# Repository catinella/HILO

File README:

#-------------------------------------------------------------------------------------------------------------------------------
#                                                     _   _ ___ _     ___  
#                                                    | | | |_ _| |   / _ \ 
#                                                    | |_| || || |  | | | |
#                                                    |  _  || || |__| |_| |
#                                                    |_| |_|___|_____\___/ 
#                                                     Hardware in the loop
#-------------------------------------------------------------------------------------------------------------------------------

1.0 Files
	firmware    The firmware for manager MCU
	PCB         All the PCBs used in the project
	pcSoftware  The software used to manage the HILO

2.0 Decription
	The goal of this progect is to get a device that allows you to test an electronic system in easy way, by remote too.
	In the 1990 when I was studing at high-scool, who was designed new devices, used generic box with buttons, switches,
	leds, displays.... and so on, to emulate the external environment. Today, unfortunately, many Italian companies still use
	the same deplorable methodology! Due to this approach firmware developers cannot work from their home.

	But the smarter companies use advanced and complicated devices that allow them to test their electronic products remotely,
	in deeper and easier way. These tools are very sophisticated and programmable simulator, where they can simulate the
	external environment is realistic and releiable way. These tools class is calle HILO.

	This project want to provide an economic and very very simple HILO.

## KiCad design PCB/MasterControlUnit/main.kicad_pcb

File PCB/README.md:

## 1.0 Files

|       Files/Dirs      |                         Description                         |
|-----------------------|-------------------------------------------------------------|
| kicadCustomComponents | The KiCAD libraries for the customized symbols/footprints   |
| IOlinesManagement     | The digital I/O lines interface                             |
| ElectricProtections   | I/O Interface electric protection devices                   |
| MasterControlUnit     | The HILO's brain                                            |

## 2.0 Decription
By the hardware points of view, this HILO is composed by the following separated modules. Everyone of them is connected to
the master one using pin-headers connectors and flat-cables.

- The Master Conroller unit interface the I/O lines with the PC and perform the configured tests
- Digital I/O lines interface
- Output lines electrical protection
- (optional) Dedicated to the Analog lines PCB

### 2.1 Components documentation:
- [APS6404L-3SQR-SN](https://eu.mouser.com/datasheet/3/4815/1/APM_PSRAM_E3_QSPI%20(APS6404L-SQH%20KGD_PKG)%20v4.1.pdf)
- [ESP32 WROOM-32-UE](https://www.espressif.com/sites/default/files/documentation/esp32-wroom-32e_esp32-wroom-32ue_datasheet_en.pdf)
- [ESP32-DevKitC-V4](https://docs.espressif.com/projects/esp-idf/en/release-v4.2/esp32/hw-reference/esp32/get-started-devkitc.html)
  [(pinout)](https://docs.espressif.com/projects/esp-idf/en/v5.1/esp32/_images/esp32-devkitC-v4-pinout.png)
- [STM32F407VG](https://www.st.com/resource/en/datasheet/dm00037051.pdf)
- [STM32F407G-DISC1](https://www.st.com/resource/en/data_brief/stm32f4discovery.pdf)
- [MCP23017](https://ww1.microchip.com/downloads/en/DeviceDoc/20001952C.pdf)
- [LD1117S33TR](https://www.st.com/resource/en/datasheet/ld1117.pdf)
- [74HC138](https://www.mouser.com/datasheet/2/308/74hc138.rev1-289073.pdf?srsltid=AU7gw4Xh3rp2TDjylkHruy-TmyljhEpg-pm_lEueWOH79XHFP8UTOZmN)
- [ADA4096-2ARMZ](https://www.analog.com/en/products/ada4096-2.html)

### 2.2 Logic scheme:

## 3.0 GIT sub-modules initialization:
Some great company (e.g., Espressif) provides official KiCad symbols and footprints for their products through public GIT repositories.
To simplify project setup and avoid having to locate and download these repositories manually, I have included them as GIT submodules.
To initialize and download the required submodules, run the following command from the repository root:

	git submodule update --init --recursive

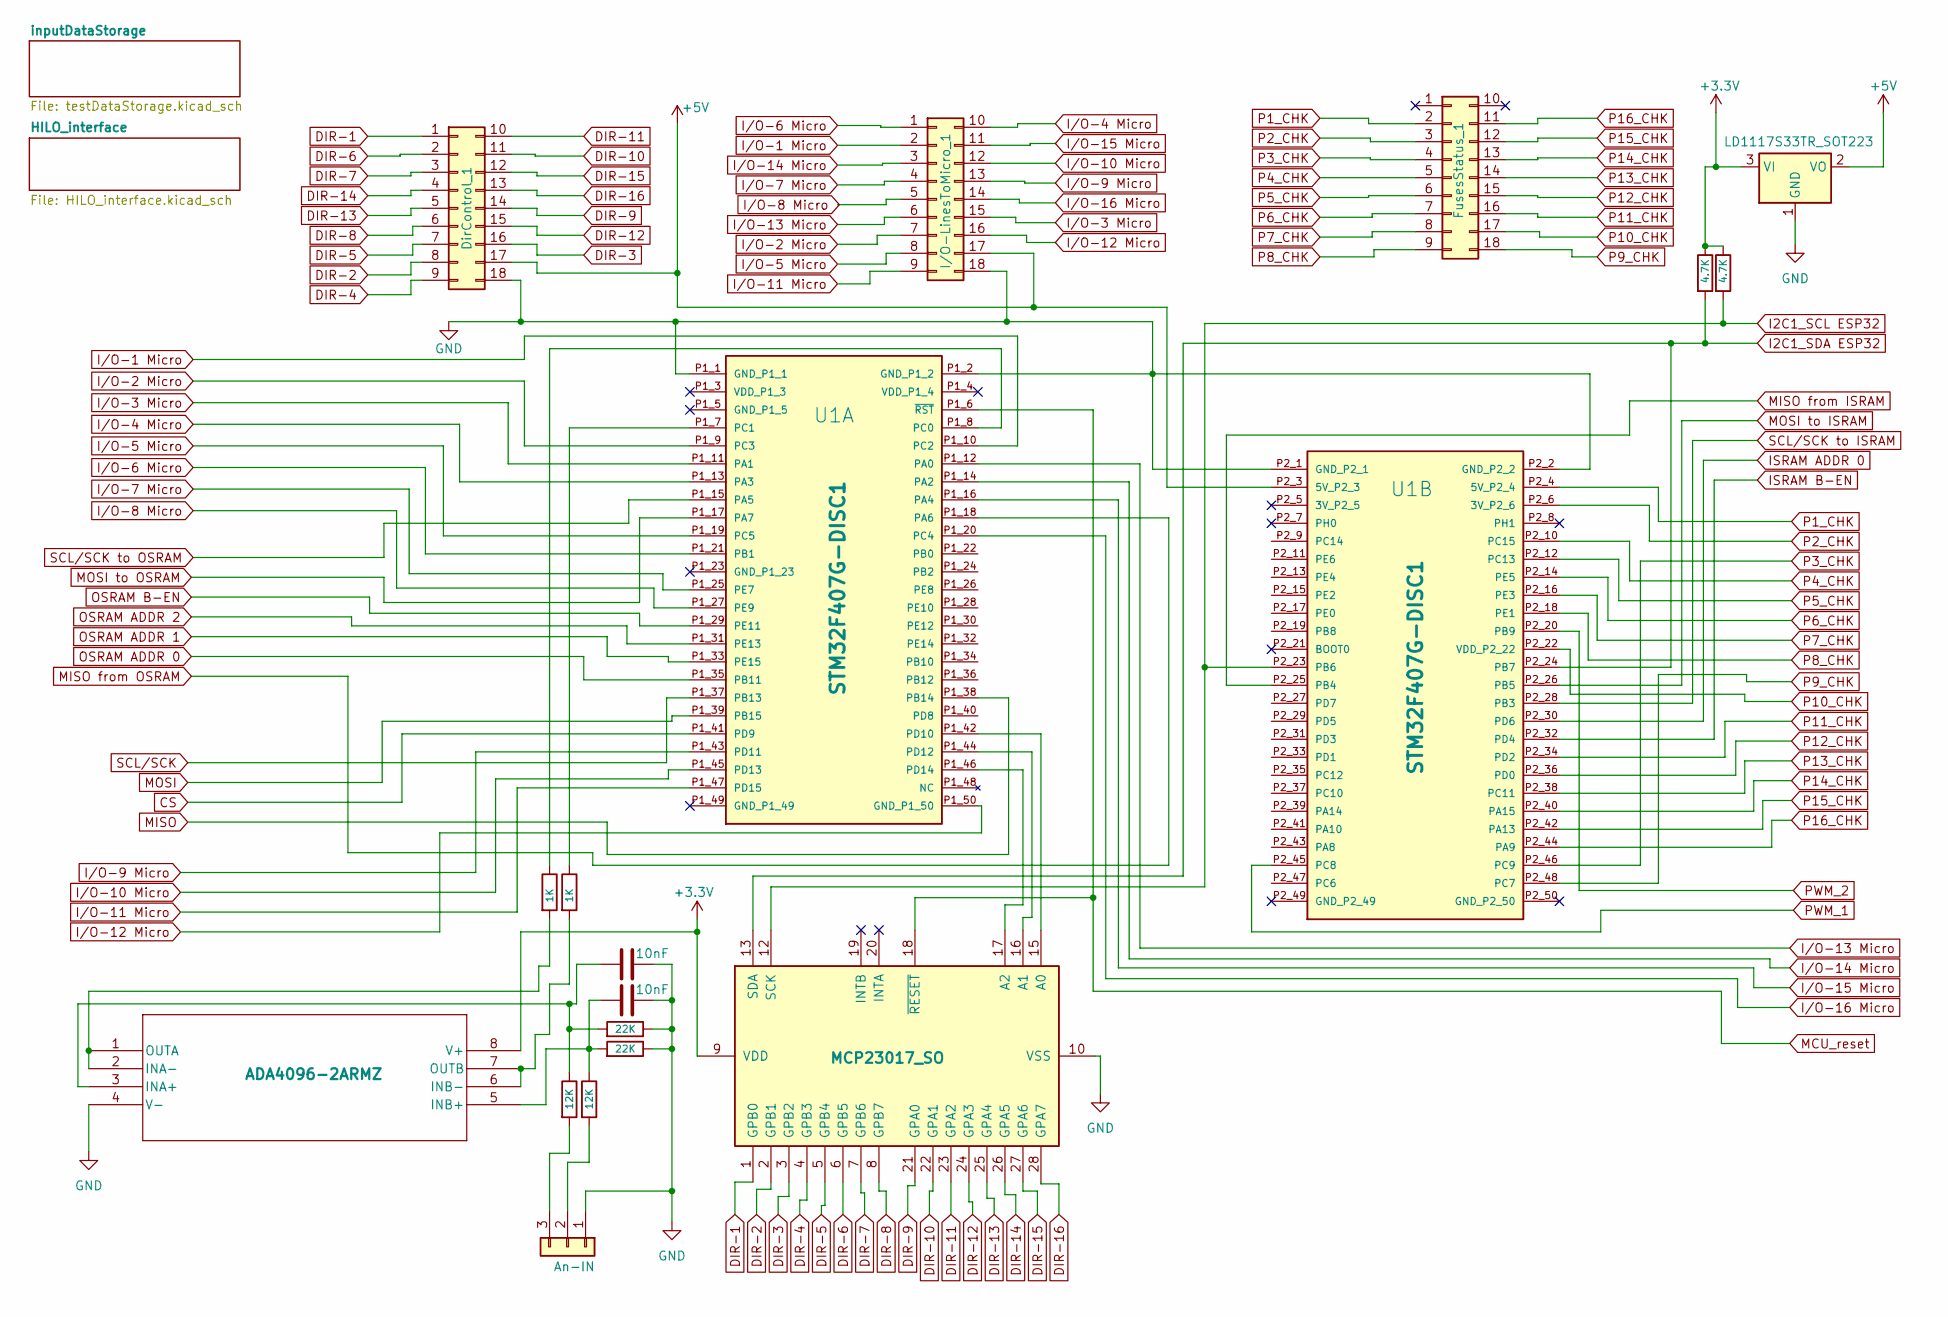
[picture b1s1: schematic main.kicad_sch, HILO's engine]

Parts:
C1, C2: 10nF; CP_Radial_D6.3mm_P2.50mm
DirControl_1: Conn_02x09_Top_Bottom; PinHeader_2x09_P2.54mm_Vertical
FusesStatus_1: Conn_02x09_Top_Bottom; PinHeader_2x09_P2.54mm_Vertical
I/O-LinesToMicro_1: Conn_02x09_Top_Bottom; PinHeader_2x09_P2.54mm_Vertical
J3: An-IN; PinHeader_1x03_P2.54mm_Vertical
R2, R3: 4.7K; R_1206_3216Metric
R4, R5: 12K; R_1206_3216Metric
R6, R7: 1K; R_1206_3216Metric
R8, R9: 22K; R_1206_3216Metric
U1: STM32F407G-DISC1; MODULE_STM32F407G-DISC1; PARTREV 7
U5: LD1117S33TR_SOT223; SOT-223-3_TabPin2
U15: MCP23017_SO; SOIC-28W_7.5x17.9mm_P1.27mm
U17: ADA4096-2ARMZ; RM_8_ADI

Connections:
CS: U1.P1_41 (PD9)
DIR-1: DirControl_1.1, U15.1 (GPB0)
DIR-2: DirControl_1.8, U15.2 (GPB1)
DIR-3: DirControl_1.16, U15.3 (GPB2)
DIR-4: DirControl_1.9, U15.4 (GPB3)
DIR-5: DirControl_1.7, U15.5 (GPB4)
DIR-6: DirControl_1.2, U15.6 (GPB5)
DIR-7: DirControl_1.3, U15.7 (GPB6)
DIR-8: DirControl_1.6, U15.8 (GPB7)
DIR-9: DirControl_1.14, U15.21 (GPA0)
DIR-10: DirControl_1.11, U15.22 (GPA1)
DIR-11: DirControl_1.10, U15.23 (GPA2)
DIR-12: DirControl_1.15, U15.24 (GPA3)
DIR-13: DirControl_1.5, U15.25 (GPA4)
DIR-14: DirControl_1.4, U15.26 (GPA5)
DIR-15: DirControl_1.12, U15.27 (GPA6)
DIR-16: DirControl_1.13, U15.28 (GPA7)
GND: C1.1, C2.1, DirControl_1.18, I/O-LinesToMicro_1.18, J3.1, R8.1, R9.1, U1.P1_1 (GND_P1_1), U1.P1_2 (GND_P1_2), U1.P2_1 (GND_P2_1), U1.P2_2 (GND_P2_2), U5.1 (GND), U15.10 (VSS), U17.4 (V-); also elsewhere on the board
I2C1_SCL ESP32: R3.2, U1.P2_23 (PB6), U15.12 (SCK); also elsewhere on the board
I2C1_SDA ESP32: R2.2, U1.P2_24 (PB7), U15.13 (SDA); also elsewhere on the board
ISRAM ADDR 0: U1.P2_30 (PD6); also elsewhere on the board
ISRAM B-EN: U1.P2_32 (PD4); also elsewhere on the board
I/O-1 Micro: I/O-LinesToMicro_1.2, U1.P1_10 (PC2)
I/O-2 Micro: I/O-LinesToMicro_1.7, U1.P1_9 (PC3)
I/O-3 Micro: I/O-LinesToMicro_1.15, U1.P1_11 (PA1)
I/O-4 Micro: I/O-LinesToMicro_1.10, U1.P1_13 (PA3)
I/O-5 Micro: I/O-LinesToMicro_1.8, U1.P1_19 (PC5)
I/O-6 Micro: I/O-LinesToMicro_1.1, U1.P1_21 (PB1)
I/O-7 Micro: I/O-LinesToMicro_1.4, U1.P1_25 (PE7)
I/O-8 Micro: I/O-LinesToMicro_1.5, U1.P1_27 (PE9)
I/O-9 Micro: I/O-LinesToMicro_1.13, U1.P1_43 (PD11)
I/O-10 Micro: I/O-LinesToMicro_1.12, U1.P1_45 (PD13)
I/O-11 Micro: I/O-LinesToMicro_1.9, U1.P1_47 (PD15)
I/O-12 Micro: I/O-LinesToMicro_1.16, U1.P1_50 (GND_P1_50)
I/O-13 Micro: I/O-LinesToMicro_1.6, U1.P1_12 (PA0)
I/O-14 Micro: I/O-LinesToMicro_1.3, U1.P1_14 (PA2)
I/O-15 Micro: I/O-LinesToMicro_1.11, U1.P1_16 (PA4)
I/O-16 Micro: I/O-LinesToMicro_1.14, U1.P1_20 (PC4)
MCU_reset: U1.P1_6 (~RST), U15.18 (~RESET); also elsewhere on the board
MISO: U1.P1_38 (PB14)
MISO from ISRAM: U1.P2_25 (PB4); also elsewhere on the board
MISO from OSRAM: U1.P1_18 (PA6); also elsewhere on the board
MOSI: U1.P1_39 (PB15)
MOSI to ISRAM: U1.P2_26 (PB5); also elsewhere on the board
MOSI to OSRAM: U1.P1_17 (PA7); also elsewhere on the board
unnamed: J3.2, R5.2
unnamed: J3.3, R4.2
unnamed: R6.1, U1.P1_8 (PC0)
unnamed: R7.1, U1.P1_7 (PC1)
unnamed: U1.P1_42 (PD10), U15.15 (A0)
unnamed: U1.P1_44 (PD12), U15.16 (A1)
unnamed: U1.P1_46 (PD14), U15.17 (A2)
unnamed: C2.2, R4.1, R9.2, U17.3 (INA+)
unnamed: R6.2, U17.1 (OUTA), U17.2 (INA-)
unnamed: C1.2, R5.1, R8.2, U17.5 (INB+)
unnamed: R7.2, U17.6 (INB-), U17.7 (OUTB)
OSRAM ADDR 0: U1.P1_35 (PB11); also elsewhere on the board
OSRAM ADDR 1: U1.P1_33 (PE15); also elsewhere on the board
OSRAM ADDR 2: U1.P1_31 (PE13); also elsewhere on the board
OSRAM B-EN: U1.P1_29 (PE11); also elsewhere on the board
P1_CHK: FusesStatus_1.2, U1.P2_4 (5V_P2_4)
P2_CHK: FusesStatus_1.3, U1.P2_6 (3V_P2_6)
P3_CHK: FusesStatus_1.4, U1.P2_46 (PC9)
P4_CHK: FusesStatus_1.5, U1.P2_10 (PC15)
P5_CHK: FusesStatus_1.6, U1.P2_12 (PC13)
P6_CHK: FusesStatus_1.7, U1.P2_14 (PE5)
P7_CHK: FusesStatus_1.8, U1.P2_16 (PE3)
P8_CHK: FusesStatus_1.9, U1.P2_18 (PE1)
P9_CHK: FusesStatus_1.18, U1.P2_48 (PC7)
P10_CHK: FusesStatus_1.17, U1.P2_22 (VDD_P2_22)
P11_CHK: FusesStatus_1.16, U1.P2_34 (PD2)
P12_CHK: FusesStatus_1.15, U1.P2_36 (PD0)
P13_CHK: FusesStatus_1.14, U1.P2_38 (PC11)
P14_CHK: FusesStatus_1.13, U1.P2_40 (PA15)
P15_CHK: FusesStatus_1.12, U1.P2_42 (PA13)
P16_CHK: FusesStatus_1.11, U1.P2_44 (PA9)
PWM_1: U1.P2_45 (PC8)
PWM_2: U1.P2_20 (PB9)
SCL/SCK: U1.P1_37 (PB13)
SCL/SCK to ISRAM: U1.P2_28 (PB3); also elsewhere on the board
SCL/SCK to OSRAM: U1.P1_15 (PA5); also elsewhere on the board

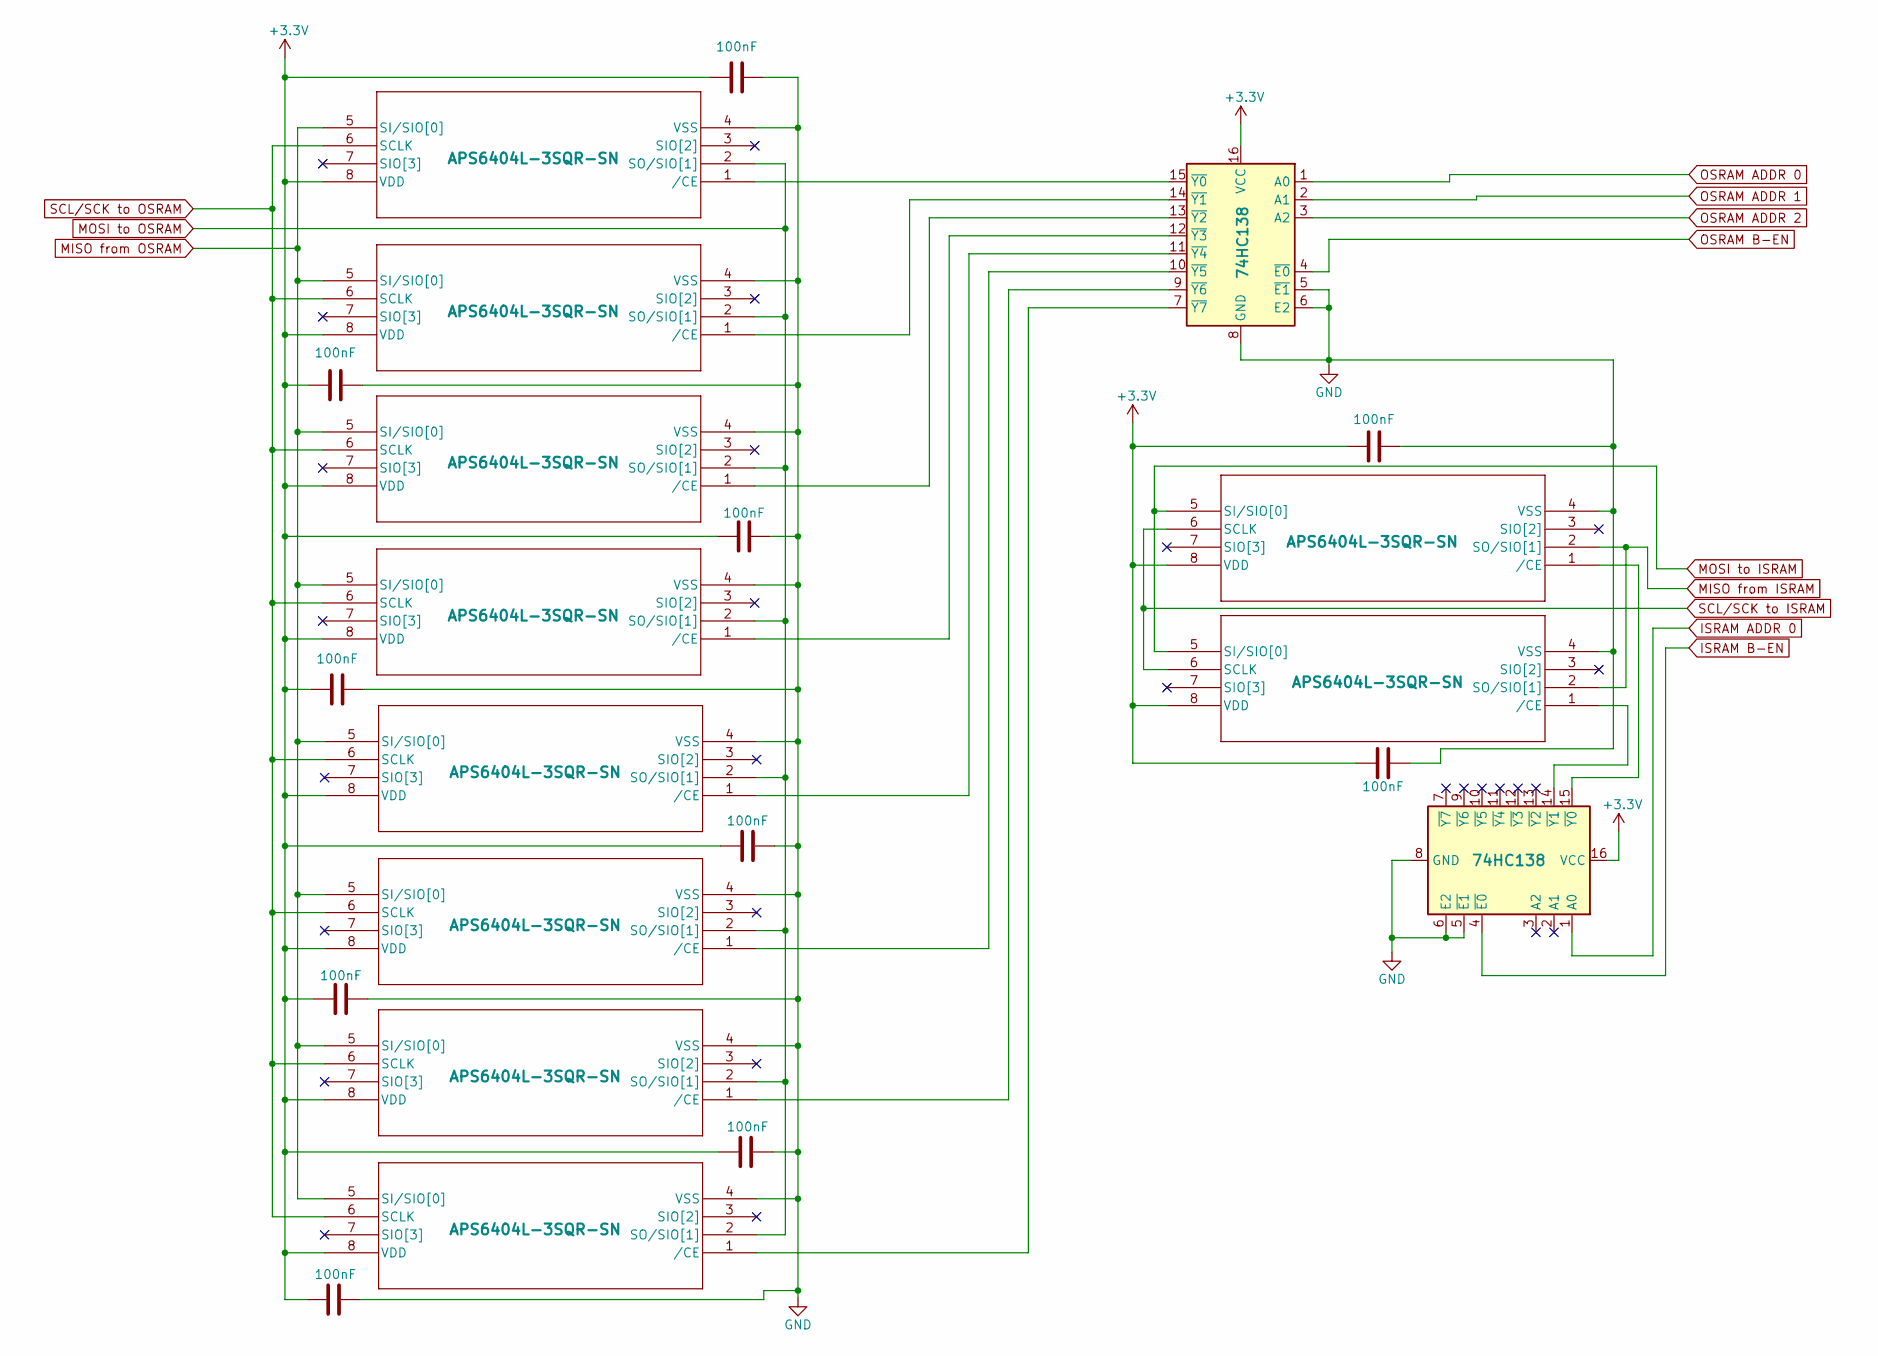
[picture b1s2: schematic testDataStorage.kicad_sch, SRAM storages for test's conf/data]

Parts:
C3, C4, C5, C6, C7, C8, C9, C10, C11, C12: 100nF; C_1206_3216Metric
U2, U3, U4, U6, U7, U8, U9, U10, U11, U12: APS6404L-3SQR-SN; APS6404L-3SQR-SN_APY
U13, U14: 74HC138; SOIC127P600X175-16N

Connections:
GND: C3.2, C4.2, C5.2, C6.2, C7.2, C8.2, C9.2, C10.2, C11.2, C12.2, U2.4 (VSS), U3.4 (VSS), U4.4 (VSS), U6.4 (VSS), U7.4 (VSS), U8.4 (VSS), U9.4 (VSS), U10.4 (VSS), U11.4 (VSS), U12.4 (VSS), U13.5 (~E1), U13.6 (E2), U13.8 (GND), U14.5 (~E1), U14.6 (E2), U14.8 (GND); also elsewhere on the board
ISRAM ADDR 0: U14.1 (A0); also elsewhere on the board
ISRAM B-EN: U14.4 (~E0); also elsewhere on the board
MISO from ISRAM: U2.2 (SO/SIO[1]), U3.2 (SO/SIO[1]); also elsewhere on the board
MISO from OSRAM: U4.5 (SI/SIO[0]), U6.5 (SI/SIO[0]), U7.5 (SI/SIO[0]), U8.5 (SI/SIO[0]), U9.5 (SI/SIO[0]), U10.5 (SI/SIO[0]), U11.5 (SI/SIO[0]), U12.5 (SI/SIO[0]); also elsewhere on the board
MOSI to ISRAM: U2.5 (SI/SIO[0]), U3.5 (SI/SIO[0]); also elsewhere on the board
MOSI to OSRAM: U4.2 (SO/SIO[1]), U6.2 (SO/SIO[1]), U7.2 (SO/SIO[1]), U8.2 (SO/SIO[1]), U9.2 (SO/SIO[1]), U10.2 (SO/SIO[1]), U11.2 (SO/SIO[1]), U12.2 (SO/SIO[1]); also elsewhere on the board
unnamed: U10.1 (/CE), U13.10 (~Y5)
unnamed: U11.1 (/CE), U13.9 (~Y6)
unnamed: U12.1 (/CE), U13.7 (~Y7)
unnamed: U4.1 (/CE), U13.15 (~Y0)
unnamed: U6.1 (/CE), U13.14 (~Y1)
unnamed: U7.1 (/CE), U13.13 (~Y2)
unnamed: U8.1 (/CE), U13.12 (~Y3)
unnamed: U9.1 (/CE), U13.11 (~Y4)
unnamed: U3.1 (/CE), U14.15 (~Y0)
unnamed: U2.1 (/CE), U14.14 (~Y1)
OSRAM ADDR 0: U13.1 (A0); also elsewhere on the board
OSRAM ADDR 1: U13.2 (A1); also elsewhere on the board
OSRAM ADDR 2: U13.3 (A2); also elsewhere on the board
OSRAM B-EN: U13.4 (~E0); also elsewhere on the board
SCL/SCK to ISRAM: U2.6 (SCLK), U3.6 (SCLK); also elsewhere on the board
SCL/SCK to OSRAM: U4.6 (SCLK), U6.6 (SCLK), U7.6 (SCLK), U8.6 (SCLK), U9.6 (SCLK), U10.6 (SCLK), U11.6 (SCLK), U12.6 (SCLK); also elsewhere on the board

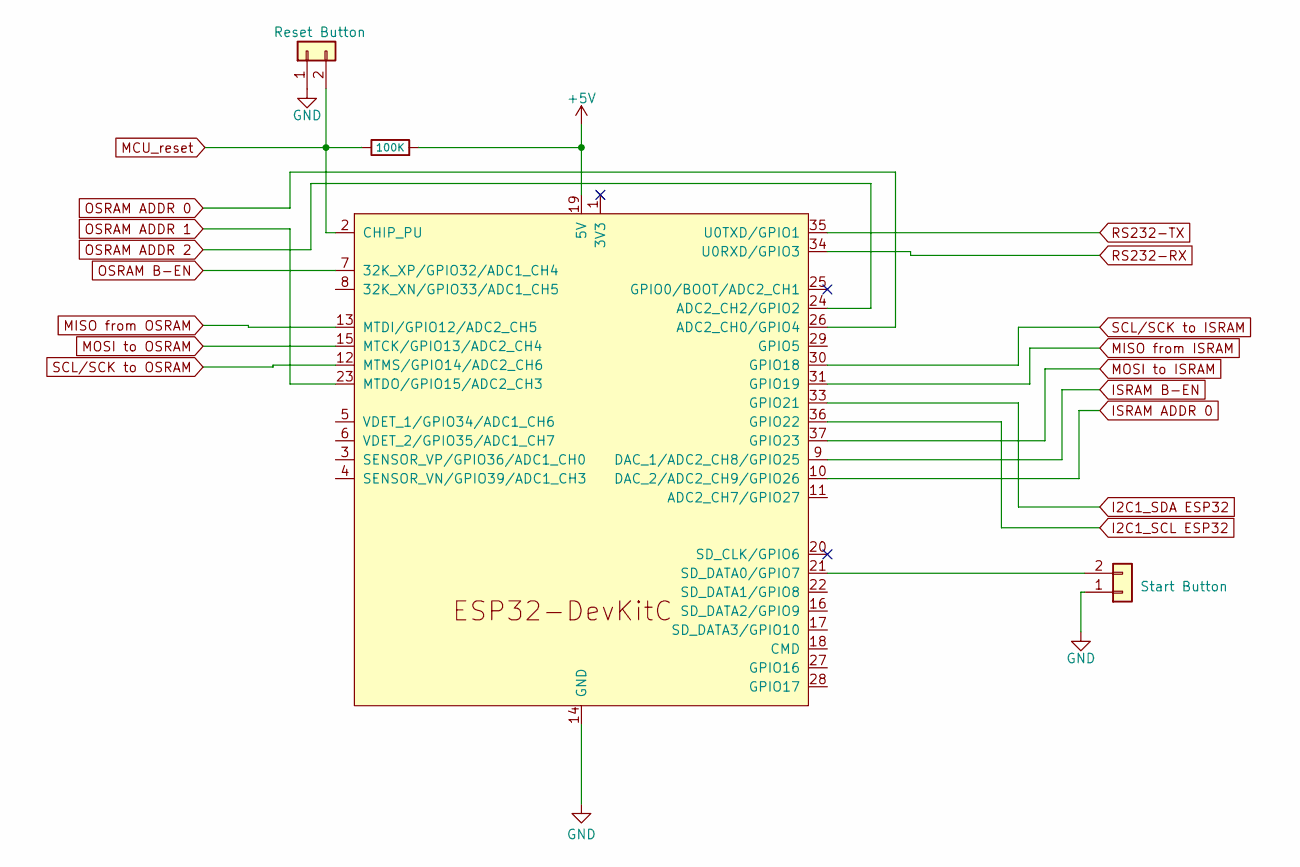
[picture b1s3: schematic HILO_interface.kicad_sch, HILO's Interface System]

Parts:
J1: Reset Button; PinHeader_1x02_P2.54mm_Vertical
J2: Start Button; PinHeader_1x02_P2.54mm_Vertical
R1: 100K; R_1206_3216Metric
U16: ESP32-DevKitC

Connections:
GND: J1.1, J2.1, U16.14 (GND), U16.32 (GND), U16.38 (GND); also elsewhere on the board
I2C1_SCL ESP32: U16.36 (GPIO22); also elsewhere on the board
I2C1_SDA ESP32: U16.33 (GPIO21); also elsewhere on the board
ISRAM ADDR 0: U16.10 (DAC_2/ADC2_CH9/GPIO26); also elsewhere on the board
ISRAM B-EN: U16.9 (DAC_1/ADC2_CH8/GPIO25); also elsewhere on the board
MCU_reset: J1.2, R1.1, U16.2 (CHIP_PU); also elsewhere on the board
MISO from ISRAM: U16.31 (GPIO19); also elsewhere on the board
MISO from OSRAM: U16.13 (MTDI/GPIO12/ADC2_CH5); also elsewhere on the board
MOSI to ISRAM: U16.37 (GPIO23); also elsewhere on the board
MOSI to OSRAM: U16.15 (MTCK/GPIO13/ADC2_CH4); also elsewhere on the board
unnamed: J2.2, U16.21 (SD_DATA0/GPIO7)
OSRAM ADDR 0: U16.26 (ADC2_CH0/GPIO4); also elsewhere on the board
OSRAM ADDR 1: U16.23 (MTDO/GPIO15/ADC2_CH3); also elsewhere on the board
OSRAM ADDR 2: U16.24 (ADC2_CH2/GPIO2); also elsewhere on the board
OSRAM B-EN: U16.7 (32K_XP/GPIO32/ADC1_CH4); also elsewhere on the board
RS232-RX: U16.34 (U0RXD/GPIO3)
RS232-TX: U16.35 (U0TXD/GPIO1)
SCL/SCK to ISRAM: U16.30 (GPIO18); also elsewhere on the board
SCL/SCK to OSRAM: U16.12 (MTMS/GPIO14/ADC2_CH6); also elsewhere on the board

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
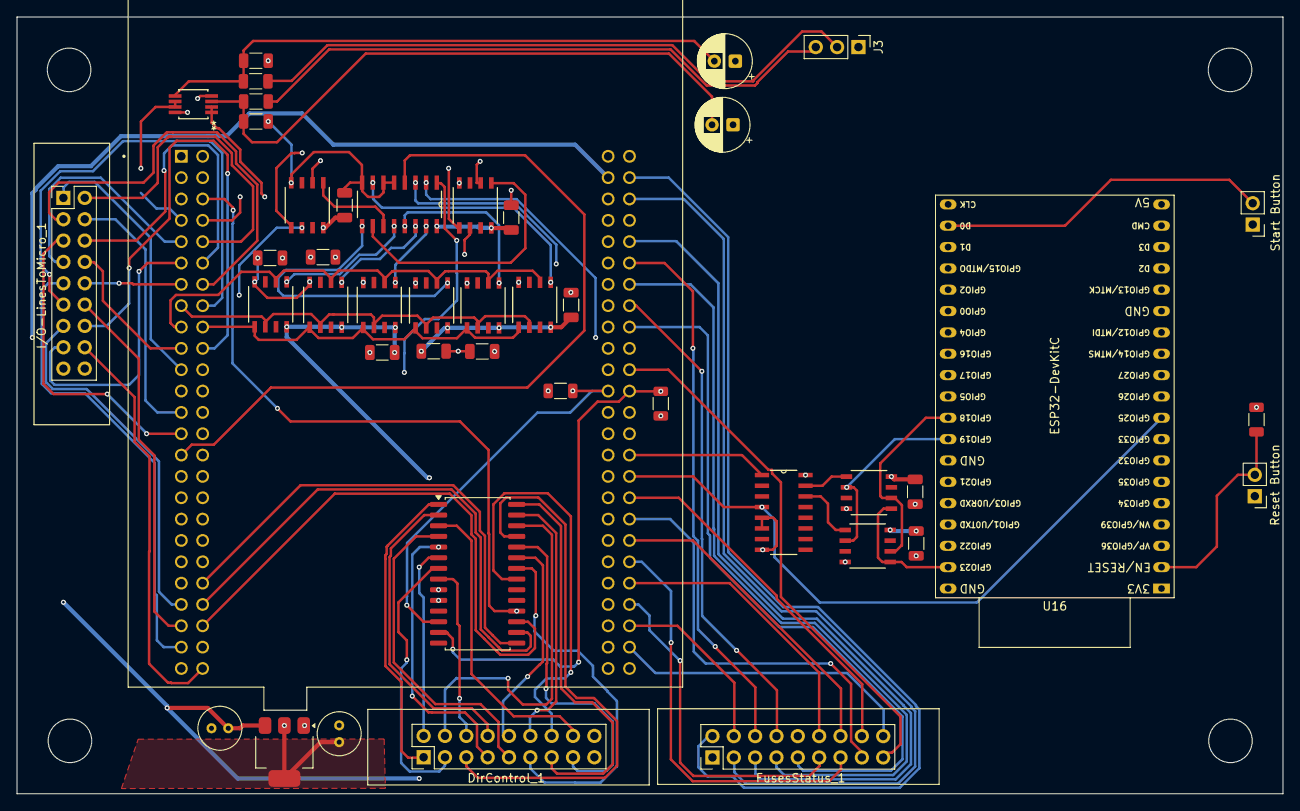
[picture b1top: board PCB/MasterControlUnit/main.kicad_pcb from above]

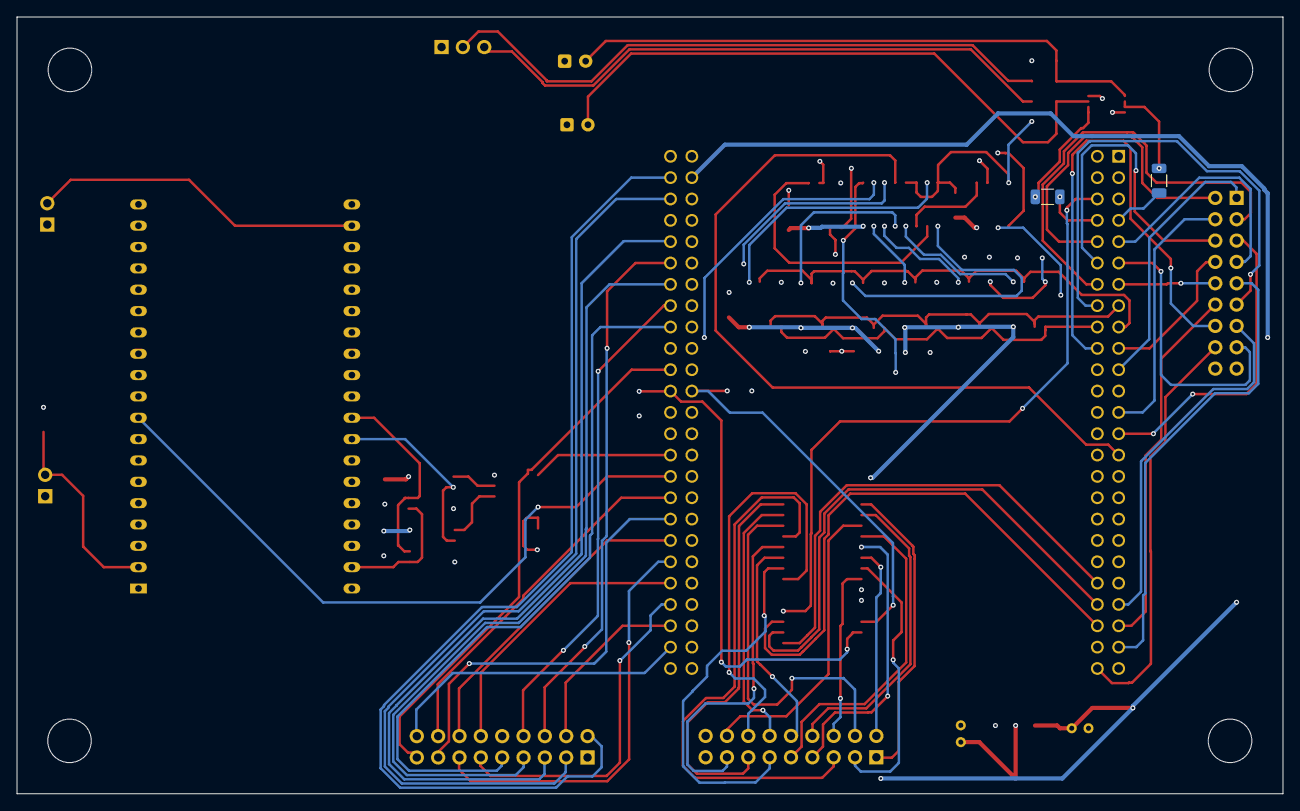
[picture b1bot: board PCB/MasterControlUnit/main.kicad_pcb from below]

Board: 4 copper layers, 150.7 x 92.4 mm, 46 parts (2 on the bottom side), 88 nets.

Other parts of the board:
C13, C14: 10uF; C_Radial_D5.0mm_H7.0mm_P2.00mm

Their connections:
GND: C13.2, C14.2; also elsewhere on the board

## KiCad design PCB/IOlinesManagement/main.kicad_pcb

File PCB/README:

#-------------------------------------------------------------------------------------------------------------------------------
#                                                     _   _ ___ _     ___  
#                                                    | | | |_ _| |   / _ \ 
#                                                    | |_| || || |  | | | |
#                                                    |  _  || || |__| |_| |
#                                                    |_| |_|___|_____\___/ 
#                                                     Hardware in the loop
#-------------------------------------------------------------------------------------------------------------------------------

1.0 Files
	kicadCustomComponents  The KiCAD libraries for the customized symbols/footprints
	IOlinesManagement      The digital I/O lines interface
	ElectricProtections    I/O Interface electric protection devices
	MasterControlUnit      The HILO's brain

2.0 Decription
	By the hardware points of view, this HILO is composed by the following separated modules. Everyone of them is connected to
	the master one using pin-headers connectors and flat-cables.
	- The Master Conroller unit interface the I/O lines with the PC and perform the configured tests
	- Digital I/O lines interface
	- Output lines electrical protection
	- (optional) Dedicated to the Analog lines PCB

	Documentation:
	==============
	APS6404L-3SQR-SN: 
		https://eu.mouser.com/datasheet/3/4815/1/APM_PSRAM_E3_QSPI%20(APS6404L-SQH%20KGD_PKG)%20v4.1.pdf
	ESP32 WROOM-32-UE:
		https://www.espressif.com/sites/default/files/documentation/esp32-wroom-32e_esp32-wroom-32ue_datasheet_en.pdf
	ESP32-DevKitC-V4:
		https://docs.espressif.com/projects/esp-idf/en/release-v4.2/esp32/hw-reference/esp32/get-started-devkitc.html
	STM32F407VG:
		https://www.st.com/resource/en/datasheet/dm00037051.pdf
	STM32F407G-DISC1:
		https://www.st.com/resource/en/data_brief/stm32f4discovery.pdf

	Logic scheme
	============

	             +------------------+----------+----------+----------+----------+....+------------------+    
	             |                  |          |          |          |          |////|                  |    
	             |     SRAM 8MB     | SRAM 8MB | SRAM 8MB | SRAM 8MB | SRAM 8MB |////|     SRAM 8MB     +-+  
	             | APS6404L-3SQR-SN | (bank1)  | (bank2)  | (bank3)  | (bank4)  |////| APS6404L-3SQR-SN | |  
	             |      (bank0)     |          |          |          |          |////|      (bank7)     | | 
	             +----------+-------+-----+----+-----+----+-----+----+----+-----+....+------------------+ |  
	                        |             |          |          |         |                               | 
	    SPI Bus ============+=============+==========+==========+=========+==+===========================+======+======
	                                                                         |                                  |
	             +------------------+----------+                             |                                  +=====+
	             |                  |          |                             |                                        |
	             |     SRAM 8MB     | SRAM 8MB |                             |                                        |
	             | APS6404L-3SQR-SN | (bank1)  |                             |                                        |
	             |      (bank0)     |          |                             |                                        |
	             +----------+-------+-----+----+                             |                                        |
	                        |             |                                  |                                        |
	    SPI Bus ============+=============+====================================+======+===                            |
	                                                                         | |      |                               |
	+-------+                                                                | |      |                               |
	|       |            +--------------+              +------------+        | |      |        +-------------+        |
	|       |  GPIO      |              |         GPIO |            | SPI(1) | |      | SPI(1) |             | SPI(3) |
	|       +<---------->+              +------------->+            +========+ |      +========+             +========+
	|       +<...DATA...>+  I/O lines   +<....DATA....>+  STM32 M4  | SPI(3)   |               |             |
	|  DUT  +<---------->+  interfaces  +<------------>+ (RealTime  +==========+               | ESP32-Wroom |
	|       |            |     and      |              |   micro)   | SPI(2)            SPI(2) | DevKitC-V4  +------+
	|       |            |  protections +------------->|            +=========<rt-data>========+ (interface) |      |
	|       |            |              +....FUSES....>|            | I2C                  I2C |             |      |
	|       |            |              +------------->|            +===========<cmds>=========+             |      |
	+-------+            |              |         GPIO |            |                          |             |      |
	                     +--------------+              +------------+                          +-------------+      |
	                                                                                                                |
	                        +---------------+                                             /\/\/\/\/\/\/\/\/\/\      |
	                        |               | REST API (tcp/ip)                           |                  |      |
	                        |               +-------------------------------------------->|                  |      |
	                        |  Test client  |                        Data stream (udp/ip) |    WiFi link     +------+
	                        |               |<--------------------------------------------+                  |
	                        |               |                                             |                  |
	                        +---------------+                                             \/\/\/\/\/\/\/\/\/\/

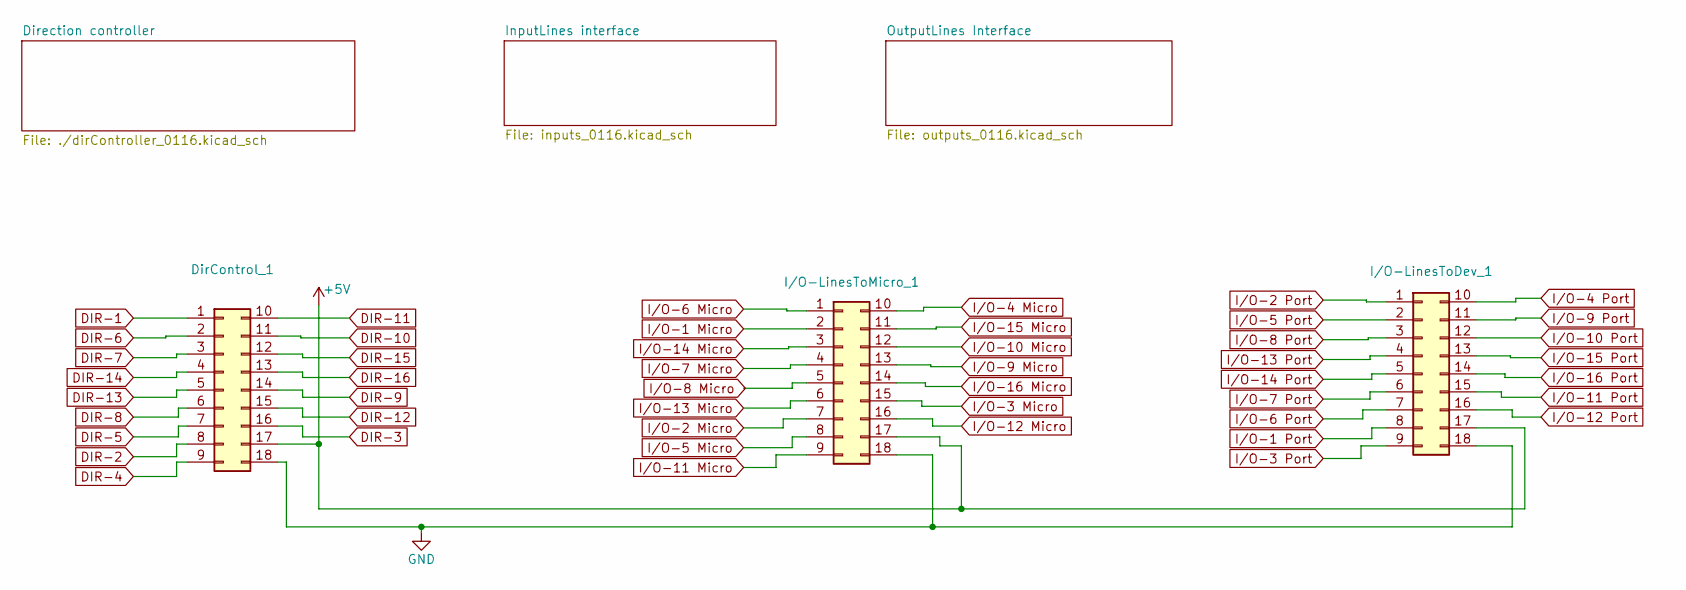
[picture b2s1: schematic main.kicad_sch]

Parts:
DirControl_1: Conn_02x09_Top_Bottom; PinHeader_2x09_P2.54mm_Vertical
I/O-LinesToDev_1: Conn_02x09_Top_Bottom; PinHeader_2x09_P2.54mm_Vertical
I/O-LinesToMicro_1: Conn_02x09_Top_Bottom; PinHeader_2x09_P2.54mm_Vertical

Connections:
+5V: DirControl_1.17, I/O-LinesToDev_1.17, I/O-LinesToMicro_1.17; also elsewhere on the board
DIR-1: DirControl_1.1; also elsewhere on the board
DIR-2: DirControl_1.8; also elsewhere on the board
DIR-3: DirControl_1.16; also elsewhere on the board
DIR-4: DirControl_1.9; also elsewhere on the board
DIR-5: DirControl_1.7; also elsewhere on the board
DIR-6: DirControl_1.2; also elsewhere on the board
DIR-7: DirControl_1.3; also elsewhere on the board
DIR-8: DirControl_1.6; also elsewhere on the board
DIR-9: DirControl_1.14; also elsewhere on the board
DIR-10: DirControl_1.11; also elsewhere on the board
DIR-11: DirControl_1.10; also elsewhere on the board
DIR-12: DirControl_1.15; also elsewhere on the board
DIR-13: DirControl_1.5; also elsewhere on the board
DIR-14: DirControl_1.4; also elsewhere on the board
DIR-15: DirControl_1.12; also elsewhere on the board
DIR-16: DirControl_1.13; also elsewhere on the board
GND: DirControl_1.18, I/O-LinesToDev_1.18, I/O-LinesToMicro_1.18; also elsewhere on the board
I/O-1 Micro: I/O-LinesToMicro_1.2; also elsewhere on the board
I/O-1 Port: I/O-LinesToDev_1.8; also elsewhere on the board
I/O-2 Micro: I/O-LinesToMicro_1.7; also elsewhere on the board
I/O-2 Port: I/O-LinesToDev_1.1; also elsewhere on the board
I/O-3 Micro: I/O-LinesToMicro_1.15; also elsewhere on the board
I/O-3 Port: I/O-LinesToDev_1.9; also elsewhere on the board
I/O-4 Micro: I/O-LinesToMicro_1.10; also elsewhere on the board
I/O-4 Port: I/O-LinesToDev_1.10; also elsewhere on the board
I/O-5 Micro: I/O-LinesToMicro_1.8; also elsewhere on the board
I/O-5 Port: I/O-LinesToDev_1.2; also elsewhere on the board
I/O-6 Micro: I/O-LinesToMicro_1.1; also elsewhere on the board
I/O-6 Port: I/O-LinesToDev_1.7; also elsewhere on the board
I/O-7 Micro: I/O-LinesToMicro_1.4; also elsewhere on the board
I/O-7 Port: I/O-LinesToDev_1.6; also elsewhere on the board
I/O-8 Micro: I/O-LinesToMicro_1.5; also elsewhere on the board
I/O-8 Port: I/O-LinesToDev_1.3; also elsewhere on the board
I/O-9 Micro: I/O-LinesToMicro_1.13; also elsewhere on the board
I/O-9 Port: I/O-LinesToDev_1.11; also elsewhere on the board
I/O-10 Micro: I/O-LinesToMicro_1.12; also elsewhere on the board
I/O-10 Port: I/O-LinesToDev_1.12; also elsewhere on the board
I/O-11 Micro: I/O-LinesToMicro_1.9; also elsewhere on the board
I/O-11 Port: I/O-LinesToDev_1.15; also elsewhere on the board
I/O-12 Micro: I/O-LinesToMicro_1.16; also elsewhere on the board
I/O-12 Port: I/O-LinesToDev_1.16; also elsewhere on the board
I/O-13 Micro: I/O-LinesToMicro_1.6; also elsewhere on the board
I/O-13 Port: I/O-LinesToDev_1.4; also elsewhere on the board
I/O-14 Micro: I/O-LinesToMicro_1.3; also elsewhere on the board
I/O-14 Port: I/O-LinesToDev_1.5; also elsewhere on the board
I/O-15 Micro: I/O-LinesToMicro_1.11; also elsewhere on the board
I/O-15 Port: I/O-LinesToDev_1.13; also elsewhere on the board
I/O-16 Micro: I/O-LinesToMicro_1.14; also elsewhere on the board
I/O-16 Port: I/O-LinesToDev_1.14; also elsewhere on the board
